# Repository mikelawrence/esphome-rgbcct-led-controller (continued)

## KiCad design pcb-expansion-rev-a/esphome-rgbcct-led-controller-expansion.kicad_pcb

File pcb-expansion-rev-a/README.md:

## ESPHome RGBCCT LED Controller Temperature Expansion PCB Rev A

This is a simple expansion board used to add both thermistor measurement and i2c expansion, mainly for off-board temperature and humidity sensors like SHTxxx devices. Rev A has a JST ZR connector for the off-board i2c temperature/humidity sensor. This PCB is also designed in [KiCad](https://www.kicad.org/). Fabrication and is again tuned toward [JCLPCB](https://jlcpcb.com/). 100% hand-soldered.

* **Rev A**: Has has fabricated, assembled and tested. No issues.

## Schematic

<p align="center">
     <br />
    Schematic
</p>

## Bill of Materials

<p align="center">
     <br />
    Interactive BOM
</p>

## PCB Info

* 2 layers, simple inexpensive PCB.
* Intended for hand-soldering.

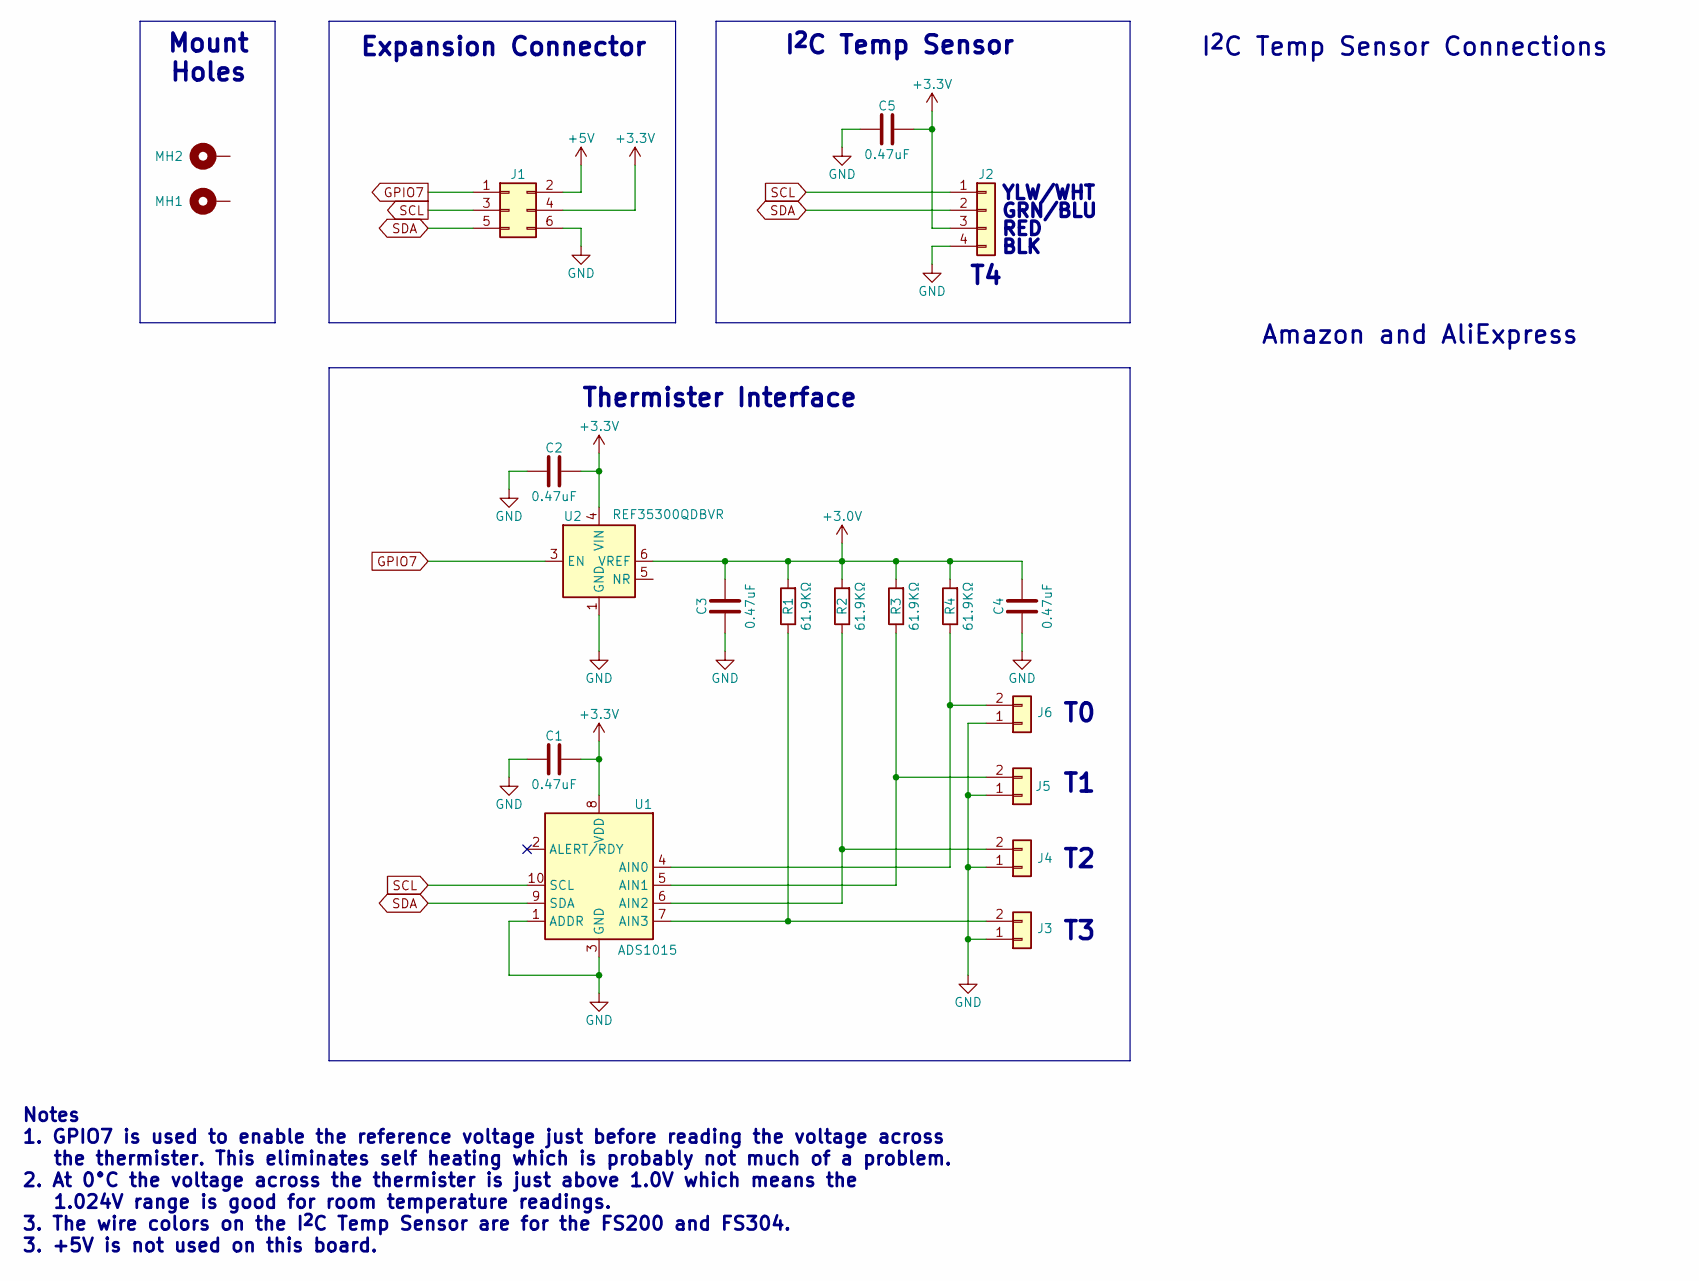
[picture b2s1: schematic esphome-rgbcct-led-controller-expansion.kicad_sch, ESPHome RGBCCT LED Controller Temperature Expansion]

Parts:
C1, C2, C3, C4, C5: 0.47uF; C_0805_2012Metric; Part Number CL21B474KAFNNNG; LCSC Part # C307331
J1: SAMTEC_SFMC-103-01-L-D; Part Number FTS-103-01-L-D
J2: Conn_01x04; JST_ZH_S4B-ZR-SM4A-TF_1x04-1MP_P1.50mm_Horizontal; Part Number S4B-ZR-SM4A-TF
J3, J4, J5, J6: Conn_01x02; JST_XH_S2B-XH-A_1x02_P2.50mm_Horizontal; Part Number S2B-XH-A(LF)(SN); LCSC Part # C157931
MH1, MH2: 97730606332R
R1, R2, R3, R4: 61.9KΩ; R_0805_2012Metric; Part Number RT0805BRD0761K9L; LCSC Part # C136977
U1: ADS1015; TSSOP-10_3x3mm_P0.5mm; Part Number ADS1015IDGSR
U2: REF35300QDBVR; SOT-23-6; Part Number REF35300QDBVR; LCSC Part # C6643299

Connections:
+3.0V: C3.1, C4.1, R1.2, R2.2, R3.2, R4.2, U2.6 (VREF)
+3.3V: C1.1, C2.2, C5.1, J1.4, J2.3, U1.8 (VDD), U2.4 (VIN)
+5V: J1.2
GND: C1.2, C2.1, C3.2, C4.2, C5.2, J1.6, J2.4, J3.1, J4.1, J5.1, J6.1, U1.1 (ADDR), U1.3 (GND), U2.1 (GND), U2.2 (GND)
GPIO7: J1.1, U2.3 (EN)
unnamed: J3.2, R1.1, U1.7 (AIN3)
unnamed: J4.2, R2.1, U1.6 (AIN2)
unnamed: J5.2, R3.1, U1.5 (AIN1)
unnamed: J6.2, R4.1, U1.4 (AIN0)
SCL: J1.3, J2.1, U1.10 (SCL)
SDA: J1.5, J2.2, U1.9 (SDA)

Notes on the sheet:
Mount Holes
Thermister Interface
BLK
RED
I^{2}C Temp Sensor
Amazon and AliExpress
GRN/BLU
Expansion Connector
YLW/WHT
I^{2}C Temp Sensor Connections
Notes 1. GPIO7 is used to enable the reference voltage just before reading the voltage across the thermister. This eliminates self heating which is probably not much of a problem. 2. At 0°C the voltage across the thermister is just above 1.0V which means the 1.024V range is good for room temperatur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

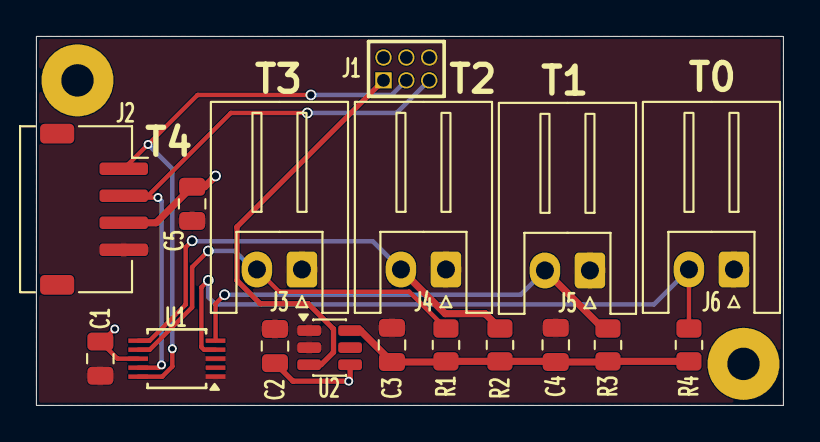
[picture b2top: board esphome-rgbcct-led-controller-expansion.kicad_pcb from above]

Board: 2 copper layers, 41.5 x 20.5 mm, 20 parts (1 on the bottom side), 10 nets.

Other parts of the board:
TEXT1: OSHW-Logo_5.7x6mm_SilkScreen

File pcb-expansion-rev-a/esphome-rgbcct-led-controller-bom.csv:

"Qty","Reference","Value","Description","Datasheet","Footprint","DNP","Manufacturer","Part Number","LCSC Part #"
"5","C1,C2,C3,C4,C5","0.47uF","Capacitor, 0.47F, MLCC, 25V, X7R, 10%, 0805","","Capacitor_SMD:C_0805_2012Metric","","Samsung","CL21B474KAFNNNG","C307331"
"1","J1","","Generic connector, double row, 02x03, odd/even pin numbering scheme (row 1 odd numbers, row 2 even numbers), script generated (kicad-library-utils/schlib/autogen/connector/)","","SAMTEC_SFMC10301LD:SAMTEC_SFMC-103-01-L-D","","Samtec","FTS-103-01-L-D",""
"1","J2","Conn_01x04","Connector, SH, 4 Pos, 1mm pitch, wire-to-board","","Connector_JST:JST_ZH_S4B-ZR-SM4A-TF_1x04-1MP_P1.50mm_Horizontal","","JST","S4B-ZR-SM4A-TF",""
"4","J3,J4,J5,J6","Conn_01x02","Connector, XH, 2 Pos, 2.5mm pitch, wire-to-board","","Connector_JST:JST_XH_S2B-XH-A_1x02_P2.50mm_Horizontal","","JST","S2B-XH-A(LF)(SN)","C157931"
"2","MH1,MH2","","Mounting Hole with connection","","97730606332R:97730606332R","","","",""
"4","R1,R2,R3,R4","61.9KΩ","Resistor, 61.9KΩ, 62.5mW, 0.1%, 25ppm, 0805","","Resistor_SMD:R_0805_2012Metric","","YAGEO","RT0805BRD0761K9L","C136977"
"1","U1","ADS1015","Ultra-Small, Low-Power, I2C-Compatible, 860-SPS, 12-Bit ADC With Internal Reference, Oscillator, and Programmable Comparator, VSSOP-10","http://www.ti.com/lit/ds/symlink/ads1013.pdf","Package_SO:TSSOP-10_3x3mm_P0.5mm","","Texas Instruments","ADS1015IDGSR",""
"1","U2","REF35300QDBVR","3.0V, Ultra Low-Power, High-Precision Voltage Reference, SOT-23-6","https://www.ti.com/lit/ds/symlink/ref35.pdf","Package_TO_SOT_SMD:SOT-23-6","","Texas Instruments","REF35300QDBVR","C6643299"

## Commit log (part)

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2026-04-08 Initial commit
    Far from fully tested
2026-04-08 Bump harm-matthias-harms/calendar-version from 3.0.1 to 3.0.2
    Bumps [harm-matthias-harms/calendar-version](https://github.com/harm-matthias-harms/calendar-version) from 3.0.1 to 3.0.2.
    - [Release notes](https://github.com/harm-matthias-harms/calendar-version/releases)
    - [Commits](https://github.com/harm-matthias-harms/calendar-version/compare/v3.0.1...v3.0.2)
    ---
    updated-dependencies:
    - dependency-name: harm-matthias-harms/calendar-version
2026-04-08 Bump actions/configure-pages from 5 to 6
    Bumps [actions/configure-pages](https://github.com/actions/configure-pages) from 5 to 6.
    - [Release notes](https://github.com/actions/configure-pages/releases)
    - [Commits](https://github.com/actions/configure-pages/compare/v5...v6)
    ---
    updated-dependencies:
    - dependency-name: actions/configure-pages
2026-04-08 Bump actions/deploy-pages from 4 to 5
    Bumps [actions/deploy-pages](https://github.com/actions/deploy-pages) from 4 to 5.
    - [Release notes](https://github.com/actions/deploy-pages/releases)
    - [Commits](https://github.com/actions/deploy-pages/compare/v4...v5)
    ---
    updated-dependencies:
    - dependency-name: actions/deploy-pages
2026-04-08 Fix several links in READMEs
2026-04-08 Add workflow_dispatch to CI configuration
2026-04-08 FIx minimum ESPHome version
2026-04-08 Rename platform from power_limited_rgbww to rgbww_power_limited in light configuration
2026-04-08 Change name from rgbcct to rgbww to reduce the length of the name.
2026-04-08 Fix missed renames
2026-04-08 Fixing Github Pages links
2026-04-09 Remove unnecessary esp32-c3 from configurations
2026-04-09 Most recent updates to ESPHome configuration
2026-04-09 Clarify fan pwm frequency.
2026-04-09 Eliminate overly verbose ina2xx logging
2026-04-09 Remove commented yaml
2026-04-09 Add .yamllint and reformat yaml
2026-04-10 Add esp32_rmt_pwm support and adjust fan PWM frequency settings
2026-04-10 Refactor YAML configuration for web server and sensor filters Slow sensors down and reduce logging
2026-04-10 Fix incorrect name
2026-04-10 Import full config when using take over
2026-04-11 Spell out Amp in friendly name
2026-04-11 Remove push trigger from CI workflow, add pull request trigger, and keep schedule trigger
2026-04-11 Remove Web Server OTA to improve security
2026-04-11 Add previous_tag input to create-release workflow
    Release notes seem to be cumulative. This change is attempt to fix this.
2026-04-11 Linting fix
2026-04-11 Add paths filter for pull request trigger in CI workflow
2026-04-11 Improve release workflows
    Create a Pre-Release and with main branch
    Attempt to build firmware
    If build is successful upload firmware and promote pre-release to release
    if build is unsuccessful remove pre-release and tag
2026-04-11 Test new github workflows, this introduces an error
2026-04-11 Correct Github workflow name
2026-04-11 Add repository context to rewind-pre-release
2026-04-11 Try another way to delete pre-release and tag
2026-04-11 Prevent Publish Pages workflow from running if Publish Firmware failed
2026-04-11 Really should be Create Release
    It starts with a Pre-Release but it end as a Release
2026-04-11 Fix error to see if workflows are still correct
2026-04-11 Update workflow trigger to use 'Create Release' instead of 'Create Pre-Release'
2026-04-11 Still trying to get promote pre-release to release working
2026-04-12 Split Expansion PCB in to Rev A and Rev B Rev A has JST ZR connector Rev B has screw terminal connectors These connectors as used by off-board i2c temperature and humidity sensor
2026-04-12 Fix README link errors
2026-04-12 Fix Rev A Interactive BOM
2026-04-12 Update Expansion Rev A Schematic Add more details for connecting sensors
2026-04-12 Update Rev B schematic pdf
2026-04-12 Update schematic image path in README
2026-04-15 Bump esphome/workflows/.github/workflows/upload-to-gh-release.yml
    Bumps [esphome/workflows/.github/workflows/upload-to-gh-release.yml](https://github.com/esphome/workflows) from 2025.10.0 to 2026.4.0.
    - [Release notes](https://github.com/esphome/workflows/releases)
    - [Commits](https://github.com/esphome/workflows/compare/2025.10.0...2026.4.0)
    ---
    updated-dependencies:
    - dependency-name: esphome/workflows/.github/workflows/upload-to-gh-release.yml
2026-04-15 Bump softprops/action-gh-release from 2 to 3
    Bumps [softprops/action-gh-release](https://github.com/softprops/action-gh-release) from 2 to 3.
    - [Release notes](https://github.com/softprops/action-gh-release/releases)
    - [Changelog](https://github.com/softprops/action-gh-release/blob/master/CHANGELOG.md)
    - [Commits](https://github.com/softprops/action-gh-release/compare/v2...v3)
    ---
    updated-dependencies:
2026-04-15 Bump esphome/workflows/.github/workflows/build.yml
    Bumps [esphome/workflows/.github/workflows/build.yml](https://github.com/esphome/workflows) from 2025.10.0 to 2026.4.0.
    - [Release notes](https://github.com/esphome/workflows/releases)
    - [Commits](https://github.com/esphome/workflows/compare/2025.10.0...2026.4.0)
    ---
    updated-dependencies:
    - dependency-name: esphome/workflows/.github/workflows/build.yml
2026-04-15 Bump actions/upload-pages-artifact from 4 to 5
    Bumps [actions/upload-pages-artifact](https://github.com/actions/upload-pages-artifact) from 4 to 5.
    - [Release notes](https://github.com/actions/upload-pages-artifact/releases)
    - [Commits](https://github.com/actions/upload-pages-artifact/compare/v4...v5)
    ---
    updated-dependencies:
    - dependency-name: actions/upload-pages-artifact
2026-04-27 Update Kicad version
2026-04-27 Ignore Kicad .history files
2026-04-27 Fix source_id on copy components
2026-04-27 YAML Linting fixes
2026-04-27 Remove development build checks in CI workflow
2026-04-27 Bump ClementTsang/delete-tag-and-release from 0.3.1 to 0.4.0
    Bumps [ClementTsang/delete-tag-and-release](https://github.com/clementtsang/delete-tag-and-release) from 0.3.1 to 0.4.0.
    - [Release notes](https://github.com/clementtsang/delete-tag-and-release/releases)
    - [Commits](https://github.com/clementtsang/delete-tag-and-release/compare/v0.3.1...v0.4.0)
    ---
    updated-dependencies:
    - dependency-name: ClementTsang/delete-tag-and-release
2026-04-27 Remove .history from .gitignore
2026-04-27 Update gitignore
2026-04-27 Remove .history folders
2026-04-27 Change cardinalby/git-get-release-action to joutvhu/get-release@v1 cardinalby/git-get-release-action has not been updated since Nove 2022 and is still using the soon to be deprecated node.js 20
2026-04-28 Finish updating to Kicad 10
2026-05-04 Fix link to PCB README in main README
2026-05-05 Add logger configuration with baud rate
    Hoping this will fix improv serial
2026-05-06 Bump esphome/workflows/.github/workflows/upload-to-gh-release.yml
    Bumps [esphome/workflows/.github/workflows/upload-to-gh-release.yml](https://github.com/esphome/workflows) from 2026.4.0 to 2026.4.1.
    - [Release notes](https://github.com/esphome/workflows/releases)
    - [Commits](https://github.com/esphome/workflows/compare/2026.4.0...2026.4.1)
    ---
    updated-dependencies:
    - dependency-name: esphome/workflows/.github/workflows/upload-to-gh-release.yml
2026-05-06 Bump esphome/workflows/.github/workflows/build.yml
    Bumps [esphome/workflows/.github/workflows/build.yml](https://github.com/esphome/workflows) from 2026.4.0 to 2026.4.1.
    - [Release notes](https://github.com/esphome/workflows/releases)
    - [Commits](https://github.com/esphome/workflows/compare/2026.4.0...2026.4.1)
    ---
    updated-dependencies:
    - dependency-name: esphome/workflows/.github/workflows/build.yml
2026-06-24 Bump actions/checkout from 6 to 7
    Bumps [actions/checkout](https://github.com/actions/checkout) from 6 to 7.
    - [Release notes](https://github.com/actions/checkout/releases)
    - [Changelog](https://github.com/actions/checkout/blob/main/CHANGELOG.md)
    - [Commits](https://github.com/actions/checkout/compare/v6...v7)
    ---
    updated-dependencies:
